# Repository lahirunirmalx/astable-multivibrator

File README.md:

# Astable Multivibrator LED Flasher

A tiny two-transistor LED flasher on a 26 x 22 mm board, built so you can
populate it from whatever parts are in your drawer. Every resistor, capacitor,
LED and transistor position accepts EITHER a through-hole part OR an SMD part,
and the transistor footprint takes a TO-92 in either common pinout (E-B-C or
C-B-E) or a SOT-23, selected with copper-only solder jumpers.

Designed in KiCad 9, DRC and ERC clean, panelized 2 x 4 with mouse bites, and
released under the MIT license. Gerbers are ready to upload.

## Features

- Classic textbook astable multivibrator: 2 transistors, 4 resistors, 2 caps, 2 LEDs
- About 1.5 Hz alternating flash with 47k / 10 uF (easy to change)
- 3 V to 9 V DC supply (5 V recommended)
- Hybrid footprints: axial 0207 or 0805 resistors, 5 mm radial or 0805 caps,
  3 mm or 0805 LEDs, TO-92 or SOT-23 transistors, all on the same pads
- Pinout-select solder jumpers: 2N3904 / PN2222 / S8050 (E-B-C) or
  BC547 / BC548 / BC337 (C-B-E) both fit the same TO-92 holes
- Minimum board area, 2 layers, GND pour both sides, copper kept 0.5 mm from
  the edge so the 2 x 4 panel can be mouse-bitten or V-cut

## Gallery

| Schematic | PCB top | PCB bottom |
|---|---|---|
|  |  |  |

| 3D top | 3D bottom | 2 x 4 panel |
|---|---|---|
|  |  |  |

Full-size schematic: [images/schematic.svg](images/schematic.svg) or
[docs/astable_multivibrator_schematic.pdf](docs/astable_multivibrator_schematic.pdf).

## Specifications

| Item | Value |
|---|---|
| Board | 26.15 x 21.73 mm, 2 layer, 1.6 mm FR4, 1 oz copper |
| Supply | 3 to 9 V DC on J1 (square pad = VCC); 5 V recommended |
| Flash rate | about 1.5 Hz (simulated 1.8 Hz at 5 V with LED drop included) |
| LED current | about 7 mA at 5 V, 15 mA at 9 V with 470 R |
| Min track / clearance | 0.3 mm tracks, 0.2 mm clearance, 0.3 mm vias |
| Fab | any standard 2-layer service (JLCPCB, PCBWay, OSH Park and friends) |
| Panel | 2 x 4 grid, 110.3 x 59.4 mm, mouse bites, 5 mm rails with tooling holes and fiducials |

## How it works

Q1 and Q2 are cross-coupled through C1 and C2. When Q1 turns on, its collector
pulls the far side of C1 low, which drives Q2's base negative and holds Q2 off.
R3 then charges C1 until Q2's base reaches 0.7 V, Q2 turns on, and the same
thing happens in mirror. Each LED sits in series with a collector resistor, so
LED1 lights while Q1 conducts and LED2 lights while Q2 conducts.

```
half period  T = 0.693 * Rb * C = 0.693 * 47k * 10u = 0.33 s   (f = 1 / 2T = 1.5 Hz)
LED current  I = (Vcc - Vf_LED - Vce_sat) / Rc = (5 - 2.0 - 0.2) / 470 = 6 mA
```

Change the speed with the timing caps: 22 uF gives about 0.7 Hz, 4.7 uF about
3.5 Hz. Above roughly 6 V the OFF transistor's base-emitter junction is briefly
driven past its reverse rating each half cycle. This is classic-kit behaviour,
harmless at these currents, but the timing drifts a little.

## Bill of materials

No part numbers on purpose. Use what you have.

| Ref | Value | Through-hole option | SMD option | Notes |
|---|---|---|---|---|
| R1, R4 | 470 R | axial 0207 (1/4 W) stood vertical | 0805 | LED series resistors |
| R2, R3 | 47k | axial 0207 stood vertical | 0805 | base bias, sets the speed |
| C1, C2 | 10 uF, 16 V or more | 5 mm radial electrolytic, 2.5 mm pitch | 0805 X5R / X7R | square pad = + |
| LED1, LED2 | red or green, 3 mm | 3 mm LED | 0805 LED | square pad = cathode (K) |
| Q1, Q2 | any general-purpose NPN | TO-92: 2N3904, 2N4401, PN2222, S8050, BC547, BC548, BC337 | SOT-23: MMBT3904, BC847, MMBT2222 | hFE 70 or more |
| J1 | 1x2 pin header 2.54 mm | pin header or just wires | - | square pad = VCC |
| JP1 to JP4 | solder jumpers | copper only, nothing to buy | | factory bridged 1-2 |

## Transistor pinout jumpers

The TO-92 centre hole is always the base. The two outer holes each pass through
a 3-pad solder jumper, so the outer legs can be swapped between emitter and
collector without a different footprint.

| Your TO-92 pinout (flat face toward you, legs down) | Example parts | What to do |
|---|---|---|
| E-B-C | 2N3904, 2N4401, PN2222, S8050 | nothing, jumpers come bridged 1-2 |
| C-B-E | BC547, BC548, BC549, BC337 | on BOTH jumpers of that transistor: cut the 1-2 trace, bridge 2-3 with solder |
| SOT-23 (any) | MMBT3904, BC847, MMBT2222 | jumpers do not matter |

JP1 and JP2 belong to Q1, JP3 and JP4 to Q2. Pad 1 = GND (emitter), pad 2 =
centre = the TO-92 outer leg, pad 3 = collector.

## Ordering boards

Upload one of these zips to your fab as a 2-layer, 1.6 mm, 1 oz board:

| What | File |
|---|---|
| Single board | [release/astable_multivibrator_gerbers_board.zip](release/astable_multivibrator_gerbers_board.zip) |
| 2 x 4 panel (8 boards per piece) | [release/astable_multivibrator_gerbers_panel_2x4.zip](release/astable_multivibrator_gerbers_panel_2x4.zip) |
| STEP model | [release/astable_multivibrator.step](release/astable_multivibrator.step) |

A filled-in PCBWay order form is in [release/PCBWAY_ORDER.md](release/PCBWAY_ORDER.md);
JLCPCB defaults work as well. For the panel choose "panel by customer" and
tell the fab the panel already contains mouse bites and rails. Any mask colour,
any finish; HASL is fine for hand soldering.

## Building it

Follow [docs/assembly.md](docs/assembly.md). Short version:

1. Decide THT or SMD per position (never both in one position).
2. Set the pinout jumpers for your TO-92 transistors (see above).
3. Solder SMD parts first, then the low parts, then the tall ones.
4. Check polarity: LED cathode and capacitor + on the square pads, TO-92 flat
   face toward the jumpers.
5. Apply 5 V to J1 (square pad = +). Both LEDs should flash alternately.

## Versions

| | v1 (this page) | v2 |
|---|---|---|
| Board | 26 x 22 mm, 2 layers, fab-made | 62 x 72 mm, 1 layer, make it at home |
| Parts | THT or SMD per position | THT only |
| Timing | fixed 47k / 10 uF | 3 x 3 selectable with header shunts |
| Pinout select | solder jumpers | pin headers with shunts |
| Files | `kicad/astable_multivibrator/`, `release/` | `kicad/astable_v2_single_layer/`, `release/v2/` |

v2 details, etching and build guide: [docs/v2_home_etching.md](docs/v2_home_etching.md).

## Simulate it in your browser

CircuitJS (falstad.com) version of the circuit, 47k / 10 uF:
[open the simulation](https://www.falstad.com/circuit/circuitjs.html?ctz=CQAgjCAMB0lwrOGAmOyDs6DMkAcyA2ATiPRHknPMgCgA3EIgkLVR5ggFih88sUqDo8GgHN2LNkxbxkUGgHcJXcAUoraSsGpArUuXd00h9hkH3VHF5uGc6cDG69NaVkfSYOvvKrlgQM-WgAnVUswiMpOdFptOW1KBIjkdxMQABMAUwAzAEMAVwAbABcAWkLM9PAeIUhkaySU7jAiOSb5LVaTVJ9uq2KTPBMPXt7EmsHjUfhmXqCaUNM9IbHzGLgF8wc7baSomJo4rYMk+wN2uSy8orKKqohBKFh6pTO+8213405P9qwAr40AYWYa+AGrB48VDGf7nGb+QJsEI2cIg1bROC0ADG4C67Ra8XQzESmVKkAEHVxhOYWFwzSJlNp9JpdNBjNZvTRHmxH1mqR+s1wBhJZIp31+QveyElUx6kou3O8PRGK0VAA8JCDpCDmtwAIIAZ2KuQARhUQABbG4ASzo1pNwVyxQA9qEADIAUQAIiBsoVcgaABaZYIAGjWAGsQAB6JAgfIAMXDpud+QGYGEIAAEgAvaAgADCgdyADtRJkQAAlZDhytYcMFsANuQuy1OrGBkDFYMgABSlZjfYLIGDuSywQNIGdJa7PbochNztywXS0BoQA).
The text dump is in [docs/circuitjs/](docs/circuitjs/) if the link ever breaks
(File > Import From Text).

## Repository layout

```
kicad/astable_multivibrator/   v1 KiCad 9 project: schematic, board, lib tables
kicad/astable_v2_single_layer/ v2 KiCad 9 project (single sided, selectable RC)
kicad/lib/Hybrid.*             v1 hybrid THT + SMD footprints and 5-pin NPN symbol
kicad/lib/HomeEtch.pretty      v2 home-etch footprints; AstableV2.kicad_sym = TO-92 socket symbol
kicad/panel/                   v1 KiKit preset, panelize.sh, panel board
kicad/tools/                   generators: footprints, 3D models, schematics, boards, routing, netlist check
images/, images/v2/            schematic, layer plots and 3D renders
docs/                          assembly guides, schematic PDFs, design check reports, spice sweep, CircuitJS
release/, release/v2/          gerber zips, STEP, print PDFs, order notes
datasheets/                    generic BOM CSV
analysis/                      analyzer outputs from the design checks
CLAUDE.md, STATUS.md           design brief and phase log of the agent workflow that produced the board
```

## Regenerating

Everything was made with KiCad 9.0.8 and scripts in `kicad/tools/`:

```
/usr/bin/python3 kicad/tools/build_hybrid_footprints.py   # hybrid footprints (pcbnew API)
/usr/bin/python3 kicad/tools/add_3d_models.py             # attach KiCad 3D models to them
python3 kicad/tools/layout_schematic.py                   # re-lay the schematic sheet
/usr/bin/python3 kicad/tools/compare_netlist.py <net> <pcb>   # schematic vs board connectivity
kicad/panel/panelize.sh                                   # KiKit 2 x 4 panel + DRC
```

v2 has its own chain (footprints, schematic, board, single-layer routing, GND pour),
listed at the end of [docs/v2_home_etching.md](docs/v2_home_etching.md).

Routing was done with Freerouting via `kicad/tools/route_freerouting.py`.

## Verification status

- ERC: 0 errors, 0 warnings.
- DRC: 0 errors, 0 unconnected. 10 warnings of type lib_footprint_mismatch
  are intentional: silk outlines that crossed SMD lands were moved to the Fab
  layer on the board only.
- Schematic vs board: all 40 pins on 12 nets match (compare_netlist.py).
- Full-circuit ngspice transient: 1.83 Hz / 7 mA at 5 V, 1.70 Hz / 15 mA at 9 V
  (see docs/check_schematic_report.md). Generic transistor and LED models.
- Independent gerber review: docs/release_review.md.

Not yet verified on a physical board. If you build one, open an issue with a
photo and the measured flash rate.

## License

MIT, see [LICENSE](LICENSE). This covers the schematic, board, footprints,
scripts and documentation in this repository.

The footprints in `kicad/lib/` are derived from the KiCad
footprint library and the 3D renders use the KiCad 3D model library. Those
libraries are licensed CC-BY-SA 4.0 with the KiCad library exception, which
allows their use in designs under any license.

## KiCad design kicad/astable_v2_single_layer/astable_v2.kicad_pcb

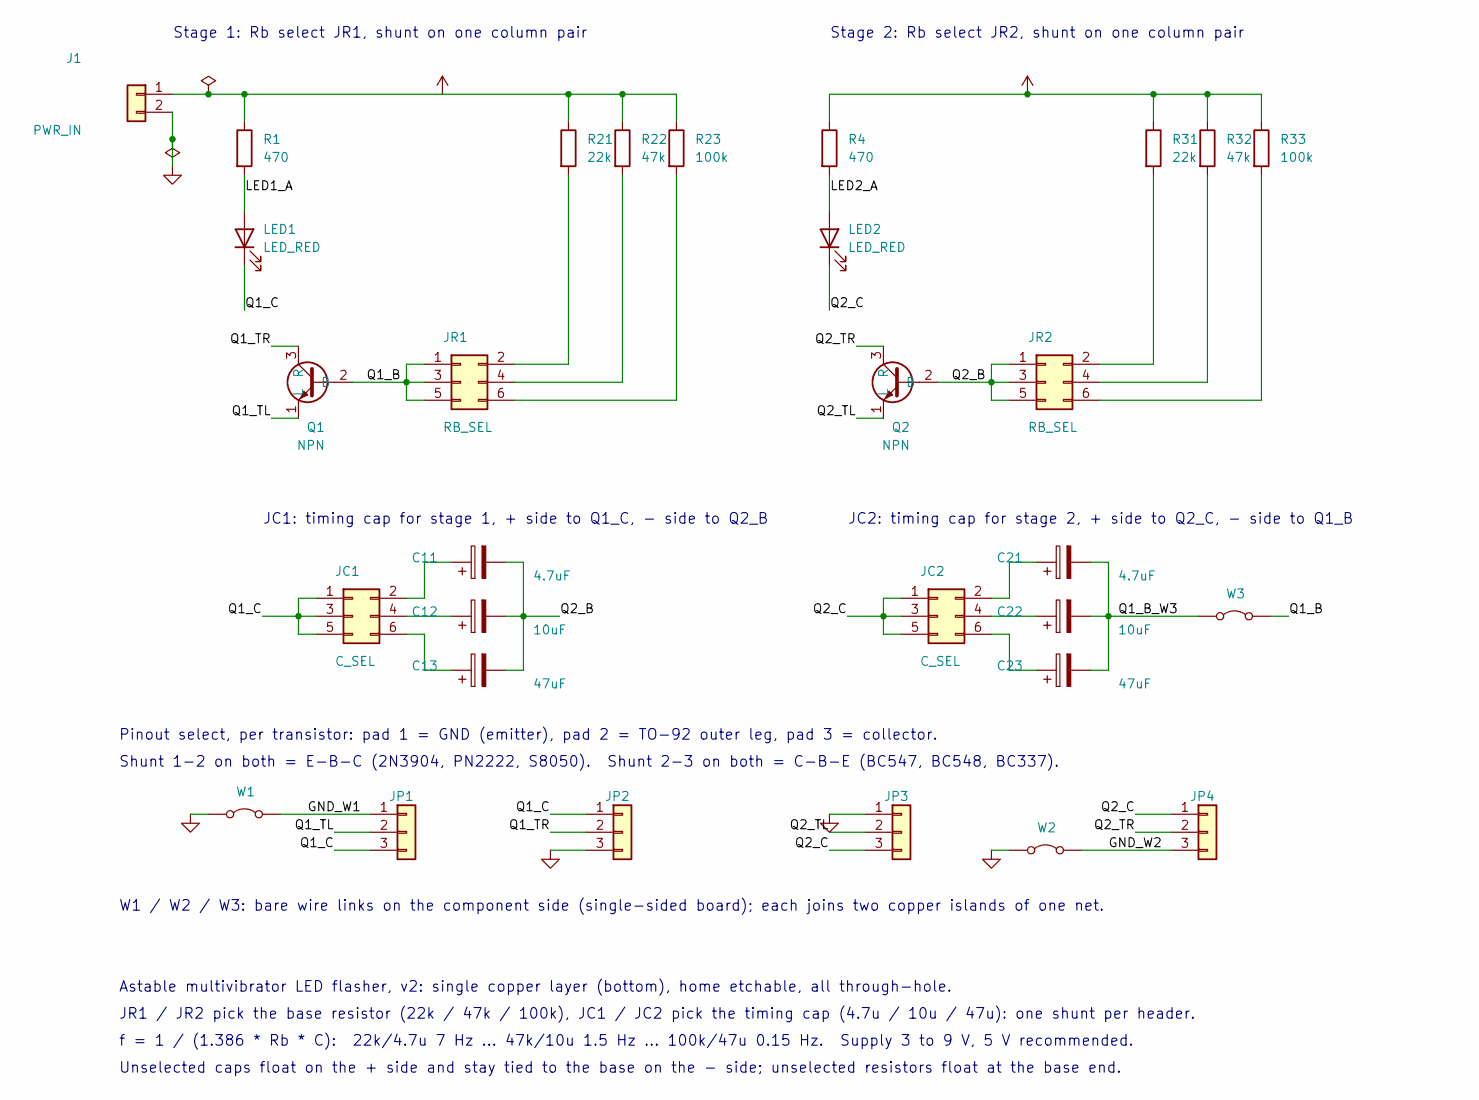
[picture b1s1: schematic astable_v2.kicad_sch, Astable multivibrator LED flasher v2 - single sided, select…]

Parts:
C11, C21: 4.7uF; CP_Radial_D6.3mm_P2.50mm_HomeEtch
C12, C22: 10uF; CP_Radial_D6.3mm_P2.50mm_HomeEtch
C13, C23: 47uF; CP_Radial_D6.3mm_P2.50mm_HomeEtch
J1: PWR_IN; PinHeader_1x02_P2.54mm_HomeEtch
JC1, JC2: C_SEL; PinHeader_2x03_P2.54mm_HomeEtch
JP1, JP2, JP3, JP4: PINOUT; PinHeader_1x03_P2.54mm_HomeEtch
JR1, JR2: RB_SEL; PinHeader_2x03_P2.54mm_HomeEtch
LED1, LED2: LED_RED; LED_D3.0mm_P2.54mm_HomeEtch
Q1, Q2: NPN; TO-92_P2.54mm_HomeEtch
R1, R4: 470; R_Axial_P10.16mm_HomeEtch
R21, R31: 22k; R_Axial_P10.16mm_HomeEtch
R22, R32: 47k; R_Axial_P10.16mm_HomeEtch
R23, R33: 100k; R_Axial_P10.16mm_HomeEtch
W1, W2: WIRE_LINK; WireLink_P12.70mm_HomeEtch
W3: WIRE_LINK; WireLink_P7.62mm_HomeEtch

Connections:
/GND_W1: JP1.1, W1.2 (B)
/GND_W2: JP4.3, W2.2 (B)
/LED1_A: LED1.2 (A), R1.2
/LED2_A: LED2.2 (A), R4.2
/Q1_B: JR1.1, JR1.3, JR1.5, Q1.2 (B), W3.2 (B)
/Q1_B_W3: C21.2, C22.2, C23.2, W3.1 (A)
/Q1_C: JC1.1, JC1.3, JC1.5, JP1.3, JP2.1, LED1.1 (K)
/Q1_TL: JP1.2, Q1.1 (L)
/Q1_TR: JP2.2, Q1.3 (R)
/Q2_B: C11.2, C12.2, C13.2, JR2.1, JR2.3, JR2.5, Q2.2 (B)
/Q2_C: JC2.1, JC2.3, JC2.5, JP3.3, JP4.1, LED2.1 (K)
/Q2_TL: JP3.2, Q2.1 (L)
/Q2_TR: JP4.2, Q2.3 (R)
GND: J1.2, JP2.3, JP3.1, W1.1 (A), W2.1 (A)
unnamed: C11.1, JC1.2
unnamed: C12.1, JC1.4
unnamed: C13.1, JC1.6
unnamed: C21.1, JC2.2
unnamed: C22.1, JC2.4
unnamed: C23.1, JC2.6
unnamed: JR1.2, R21.2
unnamed: JR1.4, R22.2
unnamed: JR1.6, R23.2
unnamed: JR2.2, R31.2
unnamed: JR2.4, R32.2
unnamed: JR2.6, R33.2
VCC: J1.1, R1.1, R4.1, R21.1, R22.1, R23.1, R31.1, R32.1, R33.1

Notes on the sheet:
Stage 1: Rb select JR1, shunt on one column pair
Stage 2: Rb select JR2, shunt on one column pair
JC1: timing cap for stage 1, + side to Q1_C, - side to Q2_B
JC2: timing cap for stage 2, + side to Q2_C, - side to Q1_B
Pinout select, per transistor: pad 1 = GND (emitter), pad 2 = TO-92 outer leg, pad 3 = collector.
Shunt 1-2 on both = E-B-C (2N3904, PN2222, S8050). Shunt 2-3 on both = C-B-E (BC547, BC548, BC337).
W1 / W2 / W3: bare wire links on the component side (single-sided board); each joins two copper islands of one net.
Astable multivibrator LED flasher, v2: single copper layer (bottom), home etchable, all through-hole.
JR1 / JR2 pick the base resistor (22k / 47k / 100k), JC1 / JC2 pick the timing cap (4.7u / 10u / 47u): one shunt per header.
f = 1 / (1.386 * Rb * C): 22k/4.7u 7 Hz ... 47k/10u 1.5 Hz ... 100k/47u 0.15 Hz. Supply 3 to 9 V, 5 V recommended.
Unselected caps float on the + side and stay tied to the base on the - side; unselected resistors float at the base end.

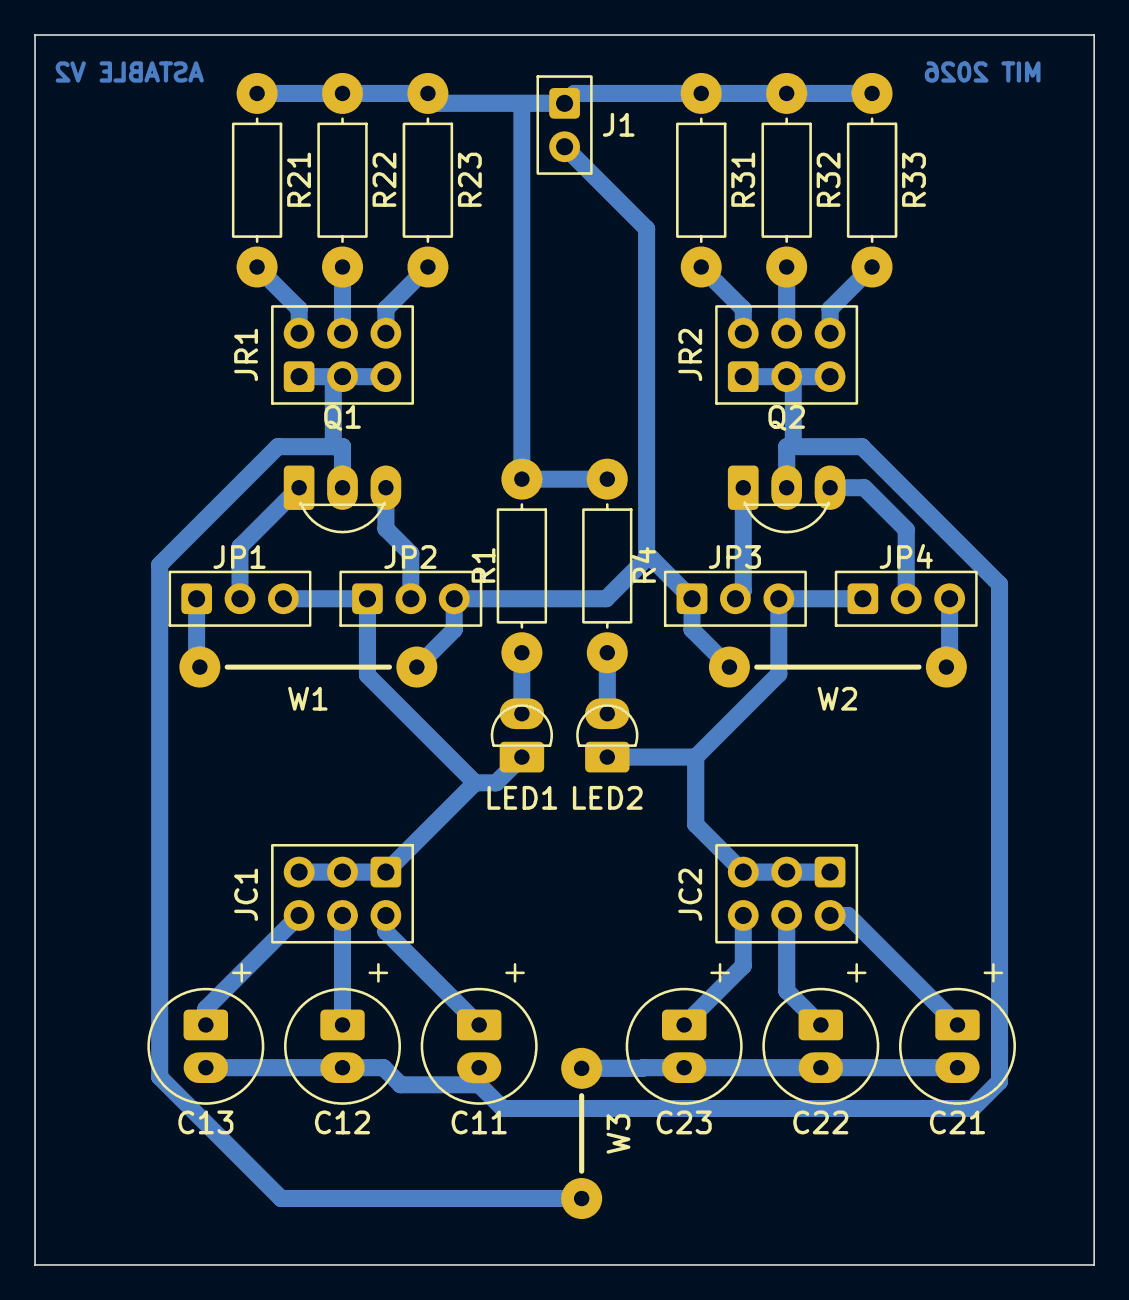
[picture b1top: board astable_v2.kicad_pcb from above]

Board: 2 copper layers, 62.0 x 72.0 mm, 30 parts (0 on the bottom side), 27 nets.

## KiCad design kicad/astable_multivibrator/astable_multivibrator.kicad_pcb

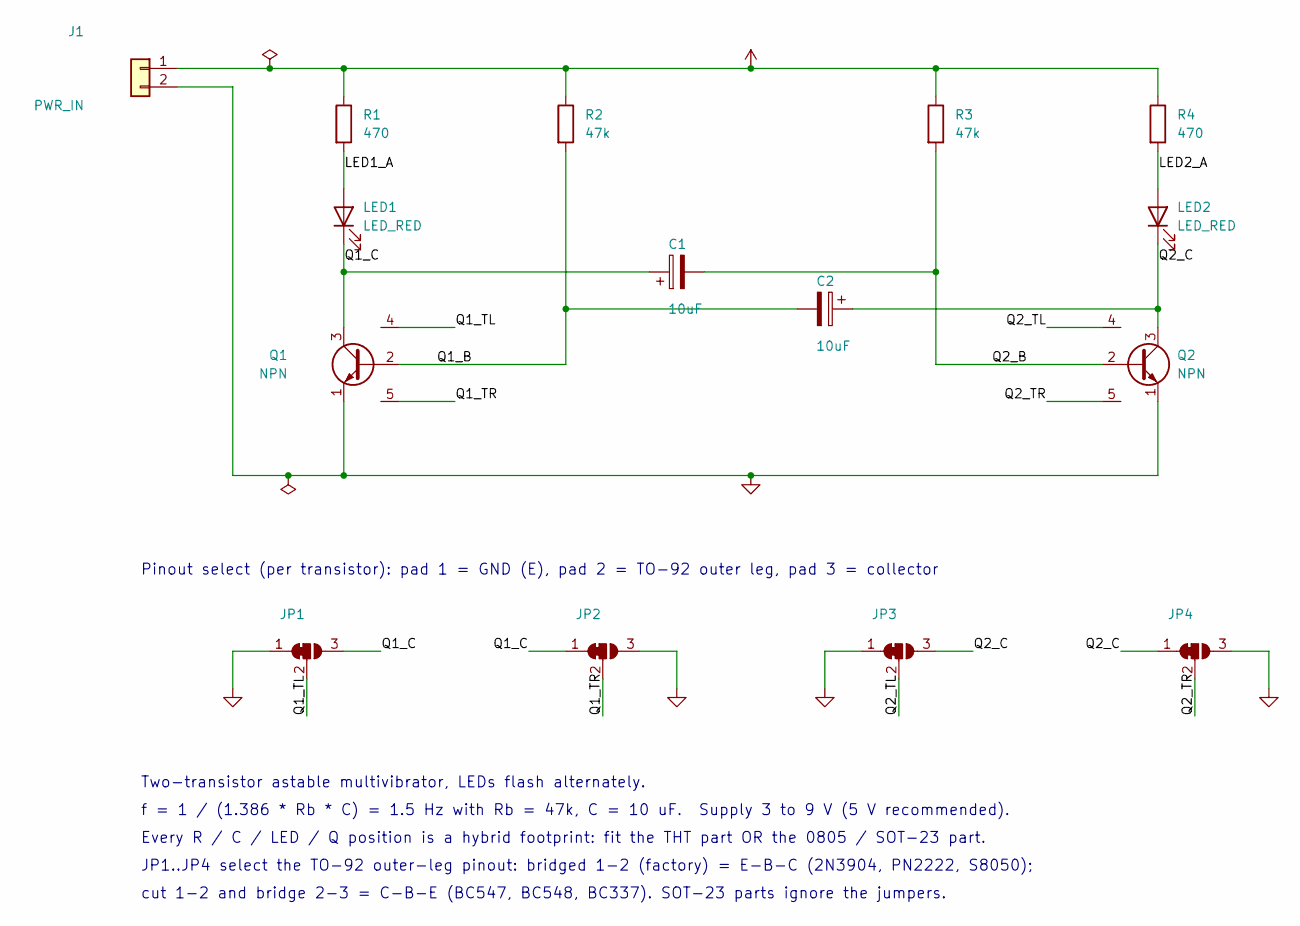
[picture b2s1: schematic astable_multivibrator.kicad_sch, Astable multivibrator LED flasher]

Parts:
C1, C2: 10uF; CP_Hybrid_0805_D5.0mm_P2.50mm
J1: PWR_IN; PinHeader_1x02_P2.54mm_Vertical
JP1, JP2, JP3, JP4: PINOUT; SolderJumper-3_P1.3mm_Bridged12_RoundedPad1.0x1.5mm
LED1, LED2: LED_RED; LED_Hybrid_0805_D3.0mm
Q1, Q2: NPN; Q_NPN_Hybrid_TO-92_SOT-23
R1, R4: 470; R_Hybrid_0805_P2.54_Vertical
R2, R3: 47k; R_Hybrid_0805_P2.54_Vertical

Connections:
/LED1_A: LED1.2 (A), R1.2
/LED2_A: LED2.2 (A), R4.2
/Q1_B: C2.2, Q1.2 (B), R2.2
/Q1_C: C1.1, JP1.3 (B), JP2.1 (A), LED1.1 (K), Q1.3 (C)
/Q1_TL: JP1.2 (C), Q1.4 (TL)
/Q1_TR: JP2.2 (C), Q1.5 (TR)
/Q2_B: C1.2, Q2.2 (B), R3.2
/Q2_C: C2.1, JP3.3 (B), JP4.1 (A), LED2.1 (K), Q2.3 (C)
/Q2_TL: JP3.2 (C), Q2.4 (TL)
/Q2_TR: JP4.2 (C), Q2.5 (TR)
GND: J1.2, JP1.1 (A), JP2.3 (B), JP3.1 (A), JP4.3 (B), Q1.1 (E), Q2.1 (E)
VCC: J1.1, R1.1, R2.1, R3.1, R4.1

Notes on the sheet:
Two-transistor astable multivibrator, LEDs flash alternately.
f = 1 / (1.386 * Rb * C) = 1.5 Hz with Rb = 47k, C = 10 uF. Supply 3 to 9 V (5 V recommended).
Every R / C / LED / Q position is a hybrid footprint: fit the THT part OR the 0805 / SOT-23 part.
JP1..JP4 select the TO-92 outer-leg pinout: bridged 1-2 (factory) = E-B-C (2N3904, PN2222, S8050);
cut 1-2 and bridge 2-3 = C-B-E (BC547, BC548, BC337). SOT-23 parts ignore the jumpers.
Pinout select (per transistor): pad 1 = GND (E), pad 2 = TO-92 outer leg, pad 3 = collector

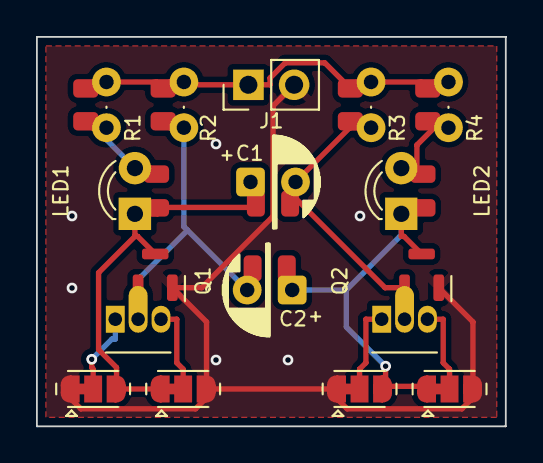
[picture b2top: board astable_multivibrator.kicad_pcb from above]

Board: 2 copper layers, 26.0 x 21.6 mm, 15 parts (0 on the bottom side), 12 nets.

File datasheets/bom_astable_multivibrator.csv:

Qty,Refs,MPN,Category,Footprint,Vendor_Status,Vendor_Stock,Vendor_Url,Datasheet
1,J1,PWR_IN,connector,Connector_PinHeader_2.54mm:PinHeader_1x02_P2.54mm_Vertical,,,,
2,R1 R4,470,generic,Hybrid:R_Hybrid_0805_P2.54_Vertical,,,,
2,LED1 LED2,LED_RED,generic,Hybrid:LED_Hybrid_0805_D3.0mm,,,,
2,R2 R3,47k,generic,Hybrid:R_Hybrid_0805_P2.54_Vertical,,,,
2,C1 C2,10uF,generic,Hybrid:CP_Hybrid_0805_D5.0mm_P2.50mm,,,,
2,Q1 Q2,NPN,generic,Hybrid:Q_NPN_Hybrid_TO-92_SOT-23,,,,
4,JP1 JP2 JP3 JP4,PINOUT,connector,Jumper:SolderJumper-3_P1.3mm_Bridged12_RoundedPad1.0x1.5mm,,,,

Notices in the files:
kicad/astable_multivibrator/astable_multivibrator.kicad_sch:
MIT licensed hobby project
